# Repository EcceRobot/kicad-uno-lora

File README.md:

# kicad-uno-lora
Arduino Uno LoRa shield. Designed with kicad.

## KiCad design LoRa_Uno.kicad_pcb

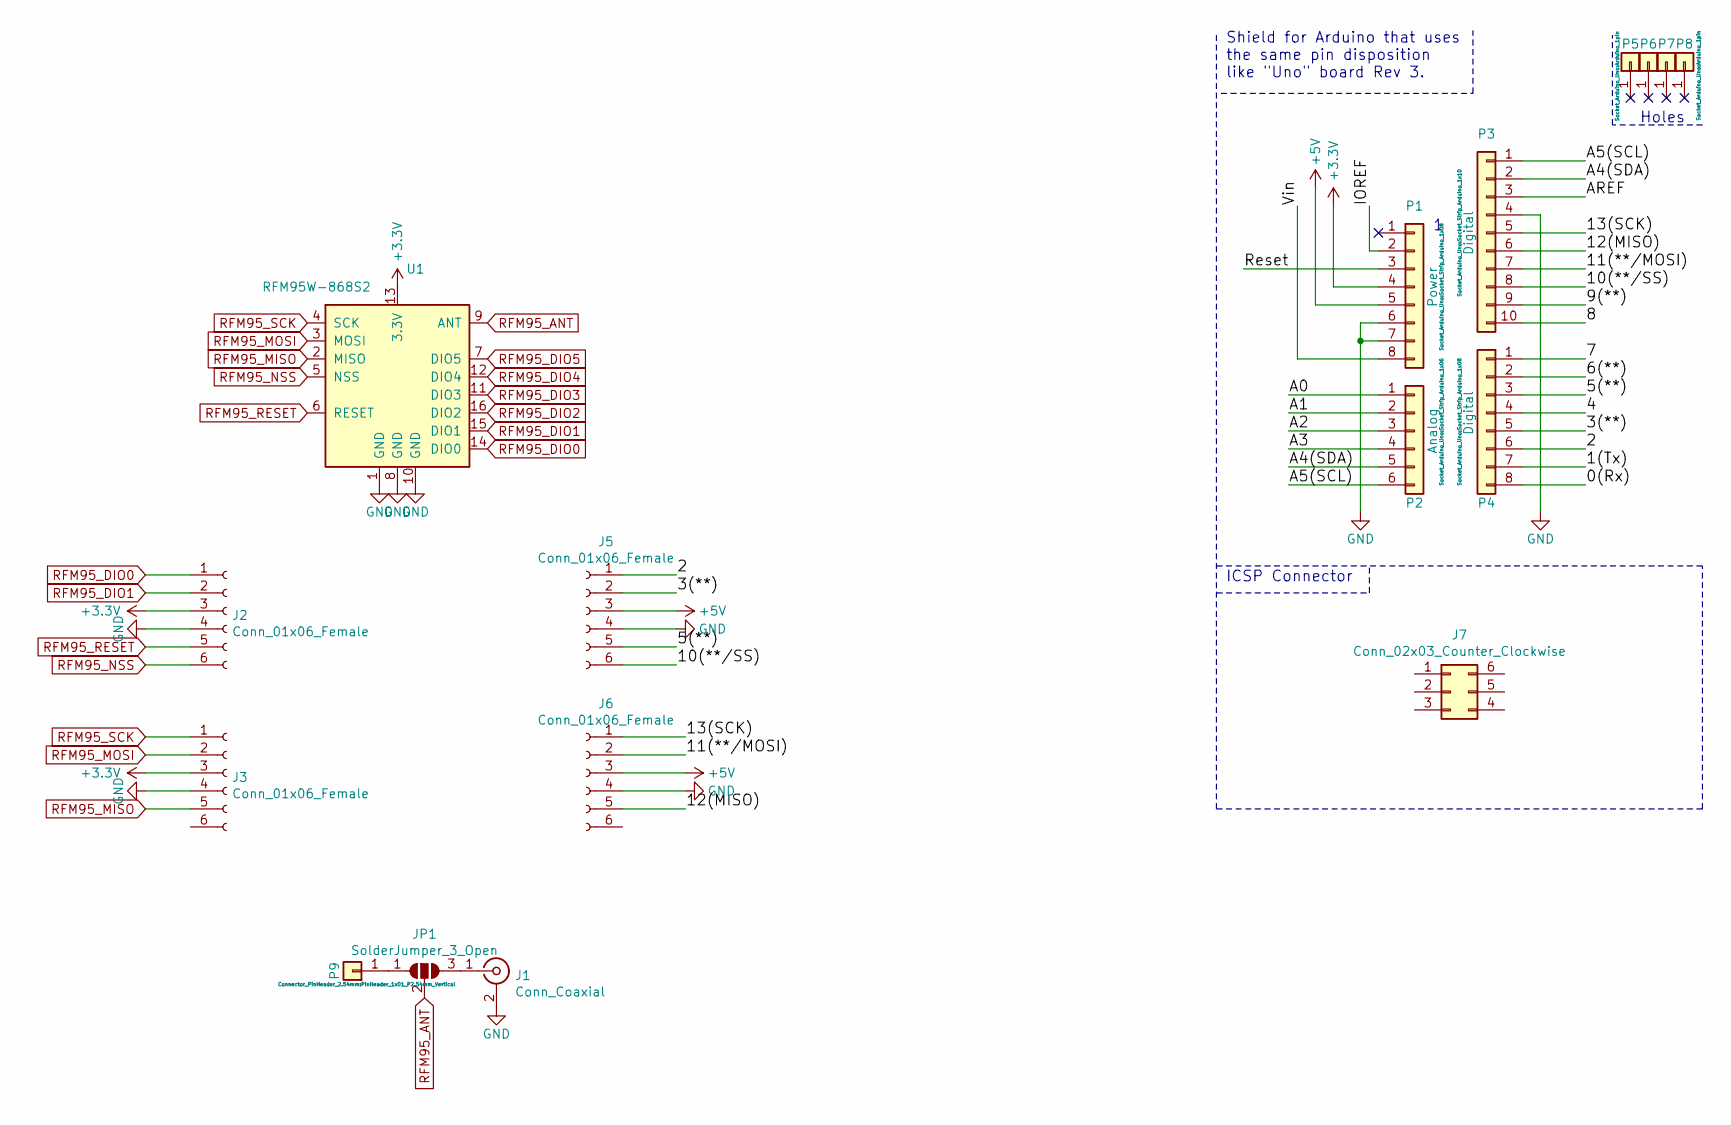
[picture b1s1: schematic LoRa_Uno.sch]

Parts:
J1: Conn_Coaxial; SMA_Molex_73251-2200_Horizontal
J2, J3, J5, J6: Conn_01x06_Female; PinHeader_1x06_P2.54mm_Vertical
J7: Conn_02x03_Counter_Clockwise; PinHeader_2x03_P2.54mm_Vertical
JP1: SolderJumper_3_Open; SolderJumper-3_P1.3mm_Open_Pad1.0x1.5mm
P1: Power; Socket_Strip_Arduino_1x08
P2: Analog; Socket_Strip_Arduino_1x06
P3: Digital; Socket_Strip_Arduino_1x10
P4: Digital; Socket_Strip_Arduino_1x08
P5, P6, P7, P8: CONN_01X01; Arduino_1pin
P9: CONN_01X01; PinHeader_1x01_P2.54mm_Vertical
U1: RFM95W-868S2; HOPERF_RFM9XW_THT

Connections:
+3V3: J2.3, J3.3, P1.4, U1.13 (3.3V)
+5V: J5.3, J6.3, P1.5
/0(Rx): P4.8
/1(Tx): P4.7
/2: J5.1, P4.6
/3(**): J5.2, P4.5
/4: P4.4
/5(**): J5.5, P4.3
/6(**): P4.2
/7: P4.1
/8: P3.10
/9(**): P3.9
/10(**/SS): J5.6, P3.8
/11(**/MOSI): J6.2, P3.7
/12(MISO): J6.5, P3.6
/13(SCK): J6.1, P3.5
/A0: P2.1
/A1: P2.2
/A2: P2.3
/A3: P2.4
/A4(SDA): P2.5, P3.2
/A5(SCL): P2.6, P3.1
/AREF: P3.3
/IOREF: P1.2
/Reset: P1.3
/Vin: P1.8
GND: J1.2 (Ext), J2.4, J3.4, J5.4, J6.4, P1.6, P1.7, P3.4, U1.1 (GND), U1.8 (GND), U1.10 (GND)
unnamed: J1.1 (In), JP1.3 (B)
unnamed: JP1.1 (A), P9.1
RFM95_ANT: JP1.2 (C), U1.9 (ANT)
RFM95_DIO0: J2.1, U1.14 (DIO0)
RFM95_DIO1: J2.2, U1.15 (DIO1)
RFM95_DIO2: U1.16 (DIO2)
RFM95_DIO3: U1.11 (DIO3)
RFM95_DIO4: U1.12 (DIO4)
RFM95_DIO5: U1.7 (DIO5)
RFM95_MISO: J3.5, U1.2 (MISO)
RFM95_MOSI: J3.2, U1.3 (MOSI)
RFM95_NSS: J2.6, U1.5 (NSS)
RFM95_RESET: J2.5, U1.6 (RESET)
RFM95_SCK: J3.1, U1.4 (SCK)

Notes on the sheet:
Holes
Shield for Arduino that uses the same pin disposition like "Uno" board Rev 3.
ICSP Connector

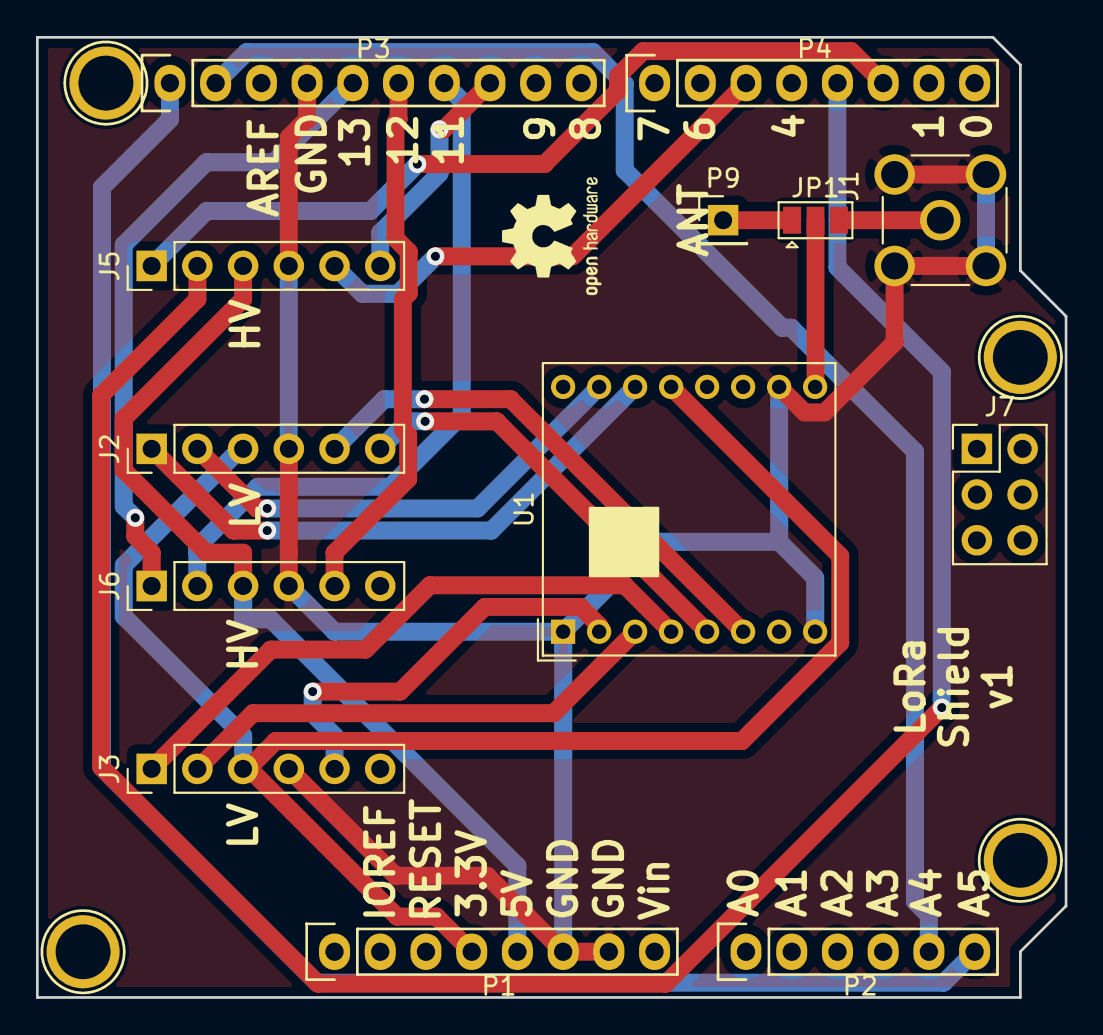
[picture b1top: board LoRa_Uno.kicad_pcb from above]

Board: 2 copper layers, 57.1 x 53.3 mm, 17 parts (0 on the bottom side), 22 nets.
